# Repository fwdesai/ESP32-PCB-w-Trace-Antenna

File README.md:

# ESP32 PCB w Trace Antenna
ESP32 based board with integrated trace antenna
v1:

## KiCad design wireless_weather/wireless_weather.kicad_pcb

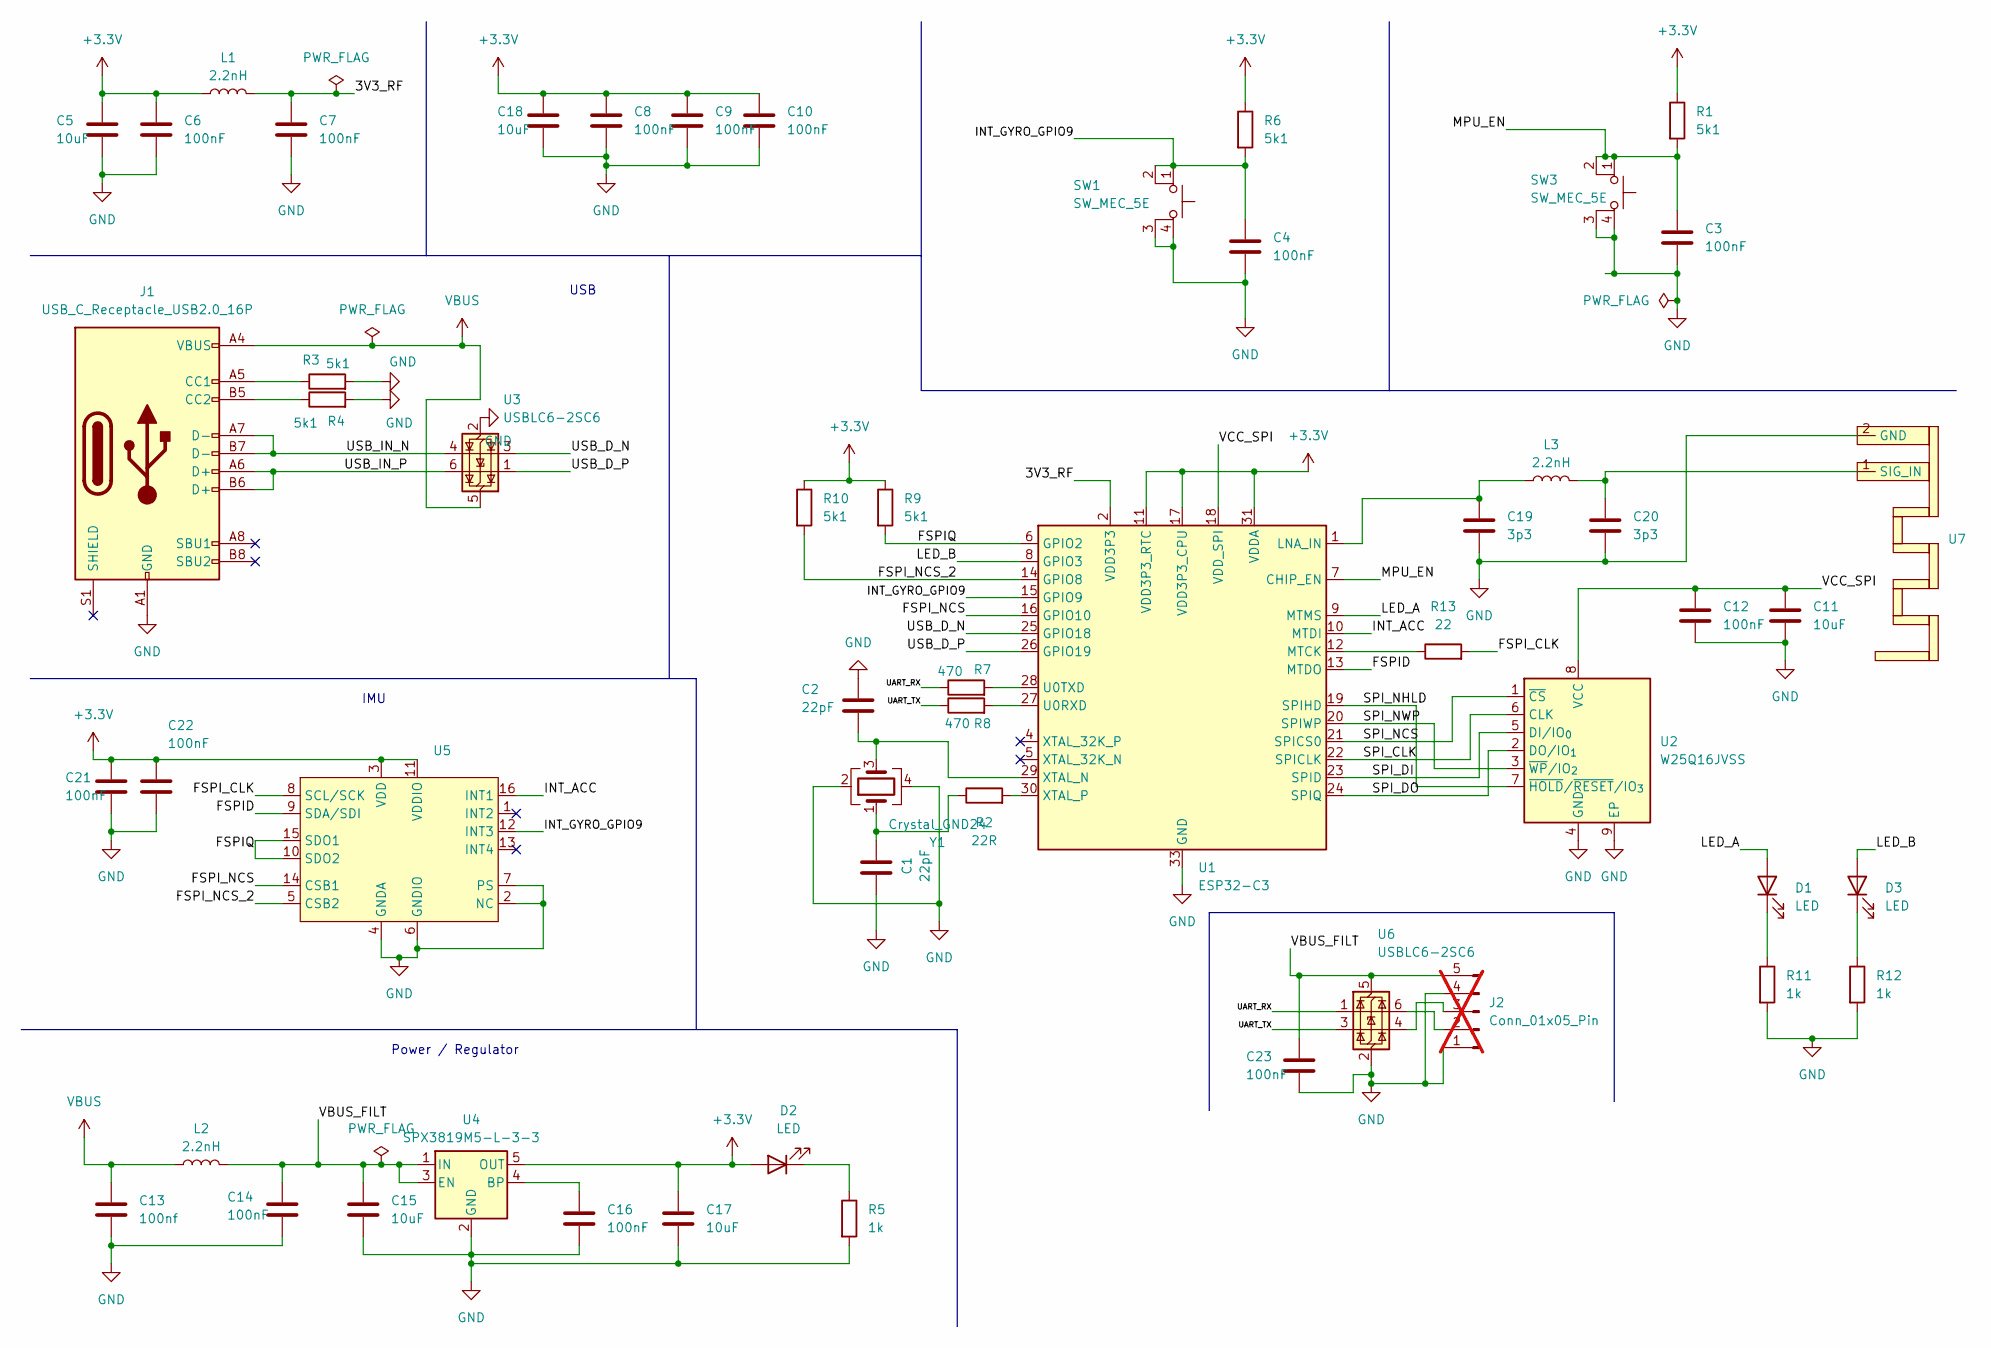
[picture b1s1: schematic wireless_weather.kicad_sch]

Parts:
C1, C2: 22pF; C_0201_0603Metric; JLC C57783
C3, C4, C6, C7, C8, C9, C10, C12, C14, C16, C21, C22, C23: 100nF; C_0201_0603Metric; JLC C49062
C5, C11, C15, C17, C18: 10uF; C_0402_1005Metric; JLC C315248
C13: 100nf; C_0201_0603Metric; JLC C49062
C19, C20: 3p3; C_0201_0603Metric; JLC C85906
D1: LED; LED_0603_1608Metric; JLC C2288
D2: LED; LED_0603_1608Metric; JLC C12624
D3: LED; LED_0603_1608Metric; JLC C2286
J1: USB_C_Receptacle_USB2.0_16P; USB_C_Receptacle_GCT_USB4105-xx-A_16P_TopMnt_Horizontal; JLC C3025063
J2: Conn_01x05_Pin; PinHeader_1x05_P2.54mm_Vertical; not fitted
L1, L2, L3: 2.2nH; L_0201_0603Metric; JLC C1329438
R1, R3, R4, R6, R9, R10: 5k1; R_0201_0603Metric; JLC C270344
R2: 22R; R_0201_0603Metric; JLC C155743
R5, R11, R12: 1k; R_0201_0603Metric; JLC C138165
R7, R8: 470; R_0201_0603Metric; JLC C473464
R13: 22; R_0201_0603Metric; JLC C155743
SW1, SW3: SW_MEC_5E; push_button; JLC C470426
U1: ESP32-C3; QFN-32-1EP_5x5mm_P0.5mm_EP3.7x3.7mm_ThermalVias; JLC C2838500
U2: W25Q16JVSS; Winbond_USON-8-1EP_3x2mm_P0.5mm_EP0.2x1.6mm; JLC C2843335
U3, U6: USBLC6-2SC6; SOT-23-6; JLC C7519
U4: SPX3819M5-L-3-3; SOT-23-5; JLC C9055
U5: bmi055; JLC C189620
U7: test
Y1: Crystal_GND24; X322540MPB4SI; JLC C9010

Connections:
+3.3V: C5.1, C6.1, C8.1, C9.1, C10.1, C17.1, C18.1, C21.1, C22.1, D2.2 (A), L1.1, R1.1, R6.1, R9.1, R10.1, U1.11 (VDD3P3_RTC), U1.17 (VDD3P3_CPU), U1.31 (VDDA), U1.32 (VDDA), U4.5 (OUT), U5.3 (VDD), U5.11 (VDDIO)
/3V3_RF: C7.1, L1.2, U1.2 (VDD3P3), U1.3 (VDD3P3)
/FSPID: U1.13 (MTDO), U5.9 (SDA/SDI)
/FSPIQ: R9.2, U1.6 (GPIO2), U5.10 (SDO2), U5.15 (SDO1)
/FSPI_CLK: R13.2, U5.8 (SCL/SCK)
/FSPI_NCS: U1.16 (GPIO10), U5.14 (CSB1)
/FSPI_NCS_2: R10.2, U1.14 (GPIO8), U5.5 (CSB2)
/INT_ACC: U1.10 (MTDI), U5.16 (INT1)
/INT_GYRO_GPIO9: C4.1, R6.2, SW1.1, SW1.2, U1.15 (GPIO9), U5.12 (INT3)
/LED_A: D1.2 (A), U1.9 (MTMS)
/LED_B: D3.2 (A), U1.8 (GPIO3)
/MPU_EN: C3.1, R1.2, SW3.1, SW3.2, U1.7 (CHIP_EN)
/SPI_CLK: U1.22 (SPICLK), U2.6 (CLK)
/SPI_DI: U1.23 (SPID), U2.5 (DI/IO_{0})
/SPI_DO: U1.24 (SPIQ), U2.2 (DO/IO_{1})
/SPI_NCS: U1.21 (SPICS0), U2.1 (~CS)
/SPI_NHLD: U1.19 (SPIHD), U2.7 (~HOLD/~RESET/IO_{3})
/SPI_NWP: U1.20 (SPIWP), U2.3 (~WP/IO_{2})
/UART_RX: R7.1, U6.1 (I/O1)
/UART_TX: R8.1, U6.3 (I/O2)
/USB_D_N: U1.25 (GPIO18), U3.3 (I/O2)
/USB_D_P: U1.26 (GPIO19), U3.1 (I/O1)
/USB_IN_N: J1.A7 (D-), J1.B7 (D-), U3.4 (I/O2)
/USB_IN_P: J1.A6 (D+), J1.B6 (D+), U3.6 (I/O1)
/VBUS_FILT: C14.1, C15.1, C23.1, J2.5, L2.2, U4.1 (IN), U4.3 (EN), U6.5 (VBUS)
/VCC_SPI: C11.1, C12.1, U1.18 (VDD_SPI), U2.8 (VCC)
GND: C1.2, C2.2, C3.2, C4.2, C5.2, C6.2, C7.2, C8.2, C9.2, C10.2, C11.2, C12.2, C13.2, C14.2, C15.2, C16.2, C17.2, C18.2, C19.2, C20.2, C21.2, C22.2, C23.2, J1.A1 (GND), J1.A12 (GND), J1.B1 (GND), J1.B12 (GND), J2.1, J2.4, R3.2, R4.2, R5.2, R11.2, R12.2, SW1.3 (K), SW1.4 (A), SW3.3 (K), SW3.4 (A), U1.33 (GND), U2.4 (GND), U2.9 (EP), U3.2 (GND), U4.2 (GND), U5.2 (NC), U5.4 (GNDA), U5.6 (GNDIO), U5.7 (PS), U6.2 (GND), U7.2 (GND), Y1.2, Y1.4
unnamed: C1.1, R2.1, Y1.1
unnamed: D1.1 (K), R11.1
unnamed: D2.1 (K), R5.1
unnamed: D3.1 (K), R12.1
unnamed: J1.A5 (CC1), R3.1
unnamed: J1.B5 (CC2), R4.1
unnamed: J2.2, U6.6 (I/O1)
unnamed: J2.3, U6.4 (I/O2)
unnamed: C19.1, L3.1, U1.1 (LNA_IN)
unnamed: R13.1, U1.12 (MTCK)
unnamed: R8.2, U1.27 (U0RXD)
unnamed: R7.2, U1.28 (U0TXD)
unnamed: C2.1, U1.29 (XTAL_N), Y1.3
unnamed: R2.2, U1.30 (XTAL_P)
unnamed: C16.1, U4.4 (BP)
unnamed: C20.1, L3.2, U7.1 (SIG_IN)
VBUS: C13.1, J1.A4 (VBUS), J1.A9 (VBUS), J1.B4 (VBUS), J1.B9 (VBUS), L2.1, U3.5 (VBUS)

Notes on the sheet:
Power / Regulator
USB
IMU

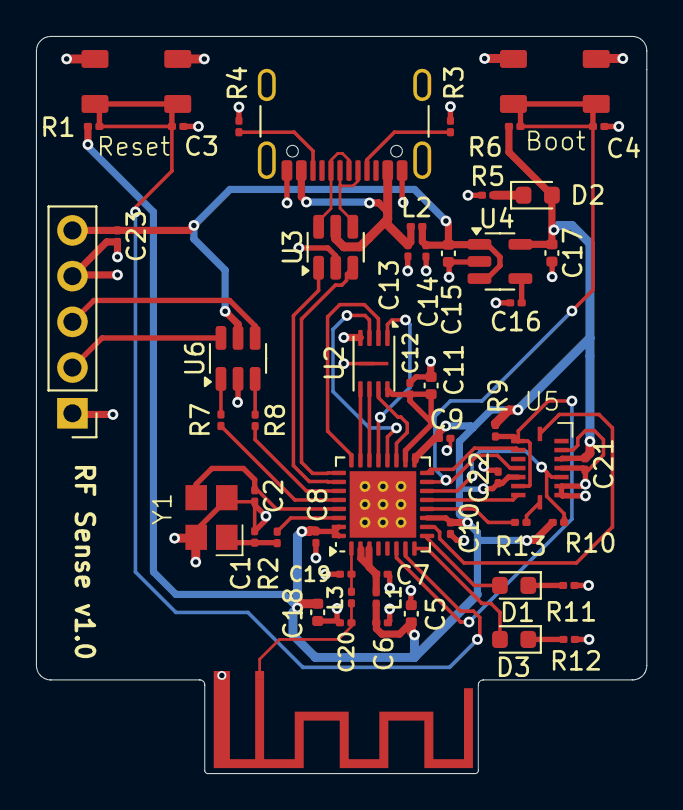
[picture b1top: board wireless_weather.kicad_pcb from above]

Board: 4 copper layers, 33.9 x 41.0 mm, 54 parts (0 on the bottom side), 44 nets.

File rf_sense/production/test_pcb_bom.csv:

Designator,Footprint,Quantity,Value,LCSC Part #
"C1, C2",0201,2,22pF,C57783
"C10, C12, C13, C14, C16, C21, C22, C23, C3, C4, C6, C7, C8, C9",0201,14,100nF,C49062
"C11, C15, C17, C18, C5",0402,5,10uF,C315248
"C19, C20",0201,2,3.3pF,C85906
D1,0603,1,LED,C2288
D2,0603,1,LED,C12624
D3,0603,1,LED,C2286
J1,USB_C_Receptacle_GCT_USB4105-xx-A_16P_TopMnt_Horizontal,1,USB_C_Receptacle_USB2.0_16P,C3025063
"L1, L2, L3",0201,3,2.2nH,C1329438
"R1, R10, R3, R4, R6, R9",0201,6,5k1,C270344
"R11, R12, R5",0201,3,1k,C138165
R13,0201,1,22R,C155743
R2,0201,1,22R,C155743
"R7, R8",0201,2,470R,C473464
"SW1, SW3",push_button,2,SW_MEC_5E,C470426
U1,QFN-32-1EP_5x5mm_P0.5mm_EP3.7x3.7mm_ThermalVias,1,ESP32-C3,C2838500
U2,Winbond_USON-8-1EP_3x2mm_P0.5mm_EP0.2x1.6mm,1,W25Q16JVSS,C2843335
"U3, U6",SOT-23-6,2,USBLC6-2SC6,C7519
U4,SOT-23-5,1,SPX3819M5-L-3-3,C9055
U5,bmi055,1,~,C189620
Y1,X322540MPB4SI,1,Crystal_GND24,C9010

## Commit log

2026-01-17 Add files via upload
    Added code to get accel info
